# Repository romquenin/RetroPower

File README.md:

# RetroPower

Home Assistant-controlled power module for retro consoles, built around an ESP32-C3 — 2-layer PCB (KiCad), with a relay that emulates the console's power button for remote on/off.

Consoles with a **real power switch** (SNES, NES, Mega Drive, Master System, N64, GameCube, Saturn, Dreamcast, PS1) use this board. Consoles with a **soft / momentary / touch button** (PS2, PS3, PS4 Pro, Xbox OG, Xbox 360, Wii, Wii U) need no PCB at all — just an ESP, one PhotoMOS and one resistor. That variant is documented in [`docs/soft-power-buttons.md`](docs/soft-power-buttons.md).

## Two PCB versions

### `hardware/integrated/` — integrated version (recommended)
The ESP32-C3-Zero module (Waveshare, 18 castellated pins, **antenna version isolated at the end of the board**, see the BOM warning) is **soldered directly to the back of the PCB** — no flying wires. The antenna ends up on the outer edge of the board, completely clear of any copper/metal on both sides, for the best possible WiFi/Bluetooth reception.

- Dimensions: 53.335 x 32.75 mm
- Official KiCad DRC: 0 errors / 0 warnings (v4)
- See `README.md` in this folder for the changelog and the pin-spacing verification procedure to run before soldering the module for good.

### `hardware/compact/` — compact version (fallback)
The ESP32-C3-Zero module is connected via flying wires (not soldered directly onto the PCB). Immune to dimensional variation between modules — useful as a fallback if the integrated version ever runs into a physical compatibility issue.

- Dimensions: 40.45 x 32.75 mm
- Official KiCad DRC: 0 errors / 0 warnings (v11)
- See `README.md` and `WIRING.md` in this folder.

Each folder contains: the `.kicad_pcb`/`.kicad_pro` files, the gerbers (folder + zip), the component position file (`_pos.csv`), the BOM (`BOM.csv`), a rendered image of the routed board, and a `README.md` explaining the design choices.

## Bill of materials

Full per-reference BOM (with placement notes) is in each version's own `BOM.csv` (`hardware/integrated/BOM.csv` / `hardware/compact/BOM.csv`). Same components and values on both versions, except J1 (compact version only, header for the flying wires to the ESP32) and the ESP32 module itself (soldered directly on the integrated version, wired via J1 on the compact one).

**On the PCB:**

| Ref | Part | Package | Notes |
|---|---|---|---|
| U1 | ESP32-C3-Zero (Waveshare) ⚠️ | 18-pin castellated module, 2.54mm pitch | **Version with the antenna at the end of the board, isolated from the other components** (see warning below). Integrated version only: soldered to the back of the PCB |
| K1 | HFD2/003-M-L2-D (Hongfa) | DIP-16 (10 real pins) | Bistable 2xRT relay |
| Q1, Q2 | AO3400A | SOT-23 | N-channel MOSFET |
| D1, D2 | 1N4148WS | SOD-123 | Flyback diodes (relay coils). **Orientation: the stripe (cathode) goes on the OPEN side of the rectangle on the silkscreen** |
| D3 | 1N5819WS | SOD-123 | Reverse-polarity protection on RAW_IN. **Orientation: the stripe (cathode) goes on the CLOSED side of the rectangle on the silkscreen** |
| R1, R2 | 100R | 0805, 1/4W 5% | Series gate resistors |
| R3, R4 | 10k | 0805, 1/4W 5% | Gate pulldowns |
| C1 | 100µF / 16V | SMD electrolytic, 6.3x5.4mm | — |
| C2 | 100nF | 0805 ceramic | HF decoupling on 3V3 |
| J1–J6 | 2.54mm pin headers | 2 to 5 pins, vertical | See each version's wiring notes |

> ⚠️ **Pick the right ESP32-C3 module.** Use the **Waveshare ESP32-C3-Zero** whose ceramic antenna sits **at the end of the board, set apart from the other components**. The PCB is designed so this antenna ends up on the outer edge, clear of any copper. Look-alike boards (clones, "ESP32-C3 Super Mini"…) where the antenna sits among the components, or a different pinout, will give poor Wi-Fi reception and may not fit the footprint. Check the product photos before ordering.

### ESP32-C3-Zero pin order (check before ordering)

The footprint matches the **pin order of the Waveshare ESP32-C3-Zero**. Some look-alike modules use the same size but a **different pin order**: with those, the power and GPIO pins end up in the wrong place. Compare your module with the order below before soldering.

Module seen **from its back side** (the side soldered to the PCB), antenna on the left, USB-C on the right:

| Row | Pins (antenna side → USB-C side) |
|---|---|
| Top (pins 10 → 18) | GP6 · GP7 · GP8 · GP9 · **GP10** · GP18 · GP19 · GP20 · GP21 |
| Bottom (pins 9 → 1) | GP5 · GP4 · **GP3** · GP2 · GP1 · **GP0** · **3V3** · **GND** · 5V |

Pins used by RetroPower:

| Module pin | Signal | Role |
|---|---|---|
| 2 · GND | GND | Common ground |
| 3 · 3V3 | 3V3 | Power from the 3.3 V buck (5V pin stays unconnected) |
| 4 · GP0 | POWER_SENSE | Reads the console state |
| 7 · GP3 | RELAY_SET | Relay SET (turn on) |
| 14 · GP10 | RELAY_RESET | Relay RESET (turn off), also drives the module's RGB LED |

<!-- Photo of the correct module (back side, pin labels visible): add it as docs/images/esp32-c3-zero-pinout.jpg and uncomment the line below.

-->

Full details and the pin-spacing check: [`hardware/integrated/README.md`](hardware/integrated/README.md).

**Off the PCB (external, per console):**

- A buck converter module (raw 12V/8V → regulated 3.3V) — any small off-the-shelf buck board rated for the console's raw voltage works; test it unloaded before wiring it in.
- Hookup wire:
  - **Power lines** (raw 12V/8V to/from the buck, regulated 3V3 to J2): 0.5mm²/20-21AWG is plenty for these currents.
  - **Signal/GPIO lines** (console switch tap to J4/J5, POWER_SENSE tap to J6): thinner wire is fine here, e.g. 30AWG — negligible current, easier to route inside the console's case.

## Firmware

ESPHome configs, in `firmware/`. Duplicate the template that matches your build and change `device_name` / `friendly_name` / the static IP — **one unique IP per console**.

| File | For |
|---|---|
| `retropower_template.yaml` | Relay board + ESP32-C3-Zero (validated on a SNES) |
| `retropower_template_esp8266.yaml` | Relay board + D1 mini (validated on a Master System) |
| `retropower_ps2.yaml` | PS2 fat — relay, momentary button |
| `retropower_megadrive.yaml` | Mega Drive — relay + Reset button (PhotoMOS on GP20) |
| `retropower_ps4.yaml` | PS4 Pro — PhotoMOS, no relay |
| `retropower_xbox_og.yaml` | Xbox OG — PhotoMOS, no relay |
| `retropower_wii.yaml` | Wii — bare ESP-12F + PhotoMOS, no relay |
| `retropower_wiiu.yaml` | Wii U — bare ESP-12F + PhotoMOS, no relay |

Pinout on the **ESP32-C3** board:

- GPIO0 — `POWER_SENSE` (reads the console's 3V3 rail)
- GPIO3 — `RELAY_SET` (100 ms pulse → turns on, via Q1)
- GPIO10 — `RELAY_RESET` (100 ms pulse → turns off, via Q2)

Same board with a **D1 mini** soldered in instead (ESP8266: GPIO0 is a boot strapping pin, GPIO3 is the serial RX and GPIO10 is not brought out, so the three pins have to move):

- GPIO14 / `D5` — `POWER_SENSE`
- GPIO5 / `D1` — `RELAY_SET`
- GPIO4 / `D2` — `RELAY_RESET`

The `D0`–`D8` labels are silkscreen only and have nothing to do with the GPIO numbers — always write the GPIO number in the YAML.

On the **no-relay** builds, a single `output` drives the PhotoMOS (`GPIO4` / `D2`, through a 470 Ω) and `GPIO14` / `D5` reads the sense. The press duration is what distinguishes power-on, standby and forced shutdown, and it has to be measured per console.

## Per-console notes

Measurements, wiring and lessons learned for each console tested so far are in [`docs/consoles/`](docs/consoles/README.md).

## Related projects

- [`projects/toslink-switch-wifi/`](projects/toslink-switch-wifi/README.md) — Wi-Fi control of a CSL 41811 Toslink audio switch (ESPHome on a D1 mini, MOSFET on the IR-jack signal line), so the audio input follows the console that is running.
- [`projects/usb-switch-wifi/`](projects/usb-switch-wifi/README.md) — Wi-Fi USB disk switch: one 2.5" Y-cable disk shared between two consoles (here a Wii U and a Wii) through two bistable relays on a D1 mini board, with a 3D-printable enclosure. The disk follows the Wii automatically and is never taken from a console that is on.

## Generation scripts (KiCad / Python)

`scripts/` contains the Python scripts (using the `pcbnew` API) used to generate and route each board, plus the verification scripts (clearance, holes, connectivity, board-edge clearance, silkscreen, component-body overlap) used alongside KiCad's official DRC.

- `scripts/integrated/`: `build_integrated.py` (placement + footprints), `route_integrated.py` (initial routing), `fix_net_integrated.py` (targeted routing fixes)
- `scripts/compact/`: `build_compact_v3.py`, `route_grid_compact5.py`
- `scripts/checks/`: verification scripts shared by both versions

Requires KiCad 7 (headless `pcbnew` API) and Python 3.

## How it works

The module emulates pressing the console's power button through two separate pulses (SET/RESET) driven by two MOSFETs (Q1/Q2) that control the two coils of a bistable relay (K1) — the relay stays in the chosen state with no continuous power draw. A sense tap (`POWER_SENSE`) lets the ESP32 read the console's actual power state for Home Assistant.

## Power supply

The buck converter (console's raw 12V/8V → regulated 3.3V) is **external**, not integrated onto the PCB. See each version's `README.md`/`WIRING.md` for the exact wiring (`J2` = regulated 3.3V input, `J3` = raw tap + reverse-polarity protection).

## Disclaimer

These files are provided as-is, with no warranty. Always re-run KiCad's official DRC before ordering a batch of PCBs, and check the 3V3 rail with a multimeter before soldering an ESP32 module in for good.

## Assembly notes (validated on a SNES, integrated board)

- **D1/D2 (flyback, 1N4148WS):** in KiCad's `D_SOD-123` footprint pad 1 is the *cathode*. The cathode must go to 3V3, so mount D1/D2 **rotated 180° vs the silkscreen** (stripe toward the 3V3 pad). **D3** is mounted as per the silkscreen.
- **GP0 (U1 pin 4) must be soldered** - it carries POWER_SENSE. Without it Home Assistant never sees the console state.
- Connect the J6 sense wire to the console's 3.3V rail; grounds must be common (buck GND on the console motherboard).
- J4: use COM (square) + NO, in parallel with the original power switch.

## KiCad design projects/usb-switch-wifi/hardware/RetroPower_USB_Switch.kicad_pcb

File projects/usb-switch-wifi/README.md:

# Wi-Fi USB disk switch

Side project, same idea as RetroPower: one 2.5" USB disk shared between two
consoles, switched over Wi-Fi.

Status: **built and working**, sharing one partitioned disk between a
**Wii U** (console 1) and a **Wii** (console 2). The disk follows the Wii
on its own: it goes to the Wii when the Wii turns on, and back to the Wii U
when it turns off.

Why: the Wii crashed when it was switched back on from standby with a USB
disk plugged in (green LED, then everything off, until the mains was
unplugged). Taking the disk away from the Wii whenever it is off removes
the problem, and sharing the disk between two consoles comes for free.

## What it does

A 2.5" disk with a Y cable has two plugs:

- **A**: 5 V + data (D+ / D-) + ground — the main plug;
- **B**: 5 V + ground only — extra current for the disk.

The board has six USB-A sockets: **A** and **B** for the disk, **A1 / B1**
toward console 1, **A2 / B2** toward console 2. Two bistable relays move
the four lines that matter together:

| Relay | Pole 1 | Pole 2 |
|---|---|---|
| K1 | D- | D+ |
| K2 | 5 V of A | 5 V of B |

Common contact on the disk side, NC (relay RESET) toward console 1,
NO (relay SET) toward console 2. Ground stays common to all six sockets.

A change-over contact opens one side before it closes the other, so the two
consoles' 5 V can never be connected together, and the console that is not
selected is completely cut off from the disk.

Same relay, same pinout and same coil driver as RetroPower: one AO3400A per
coil set, 100 Ω gate resistor, 10 kΩ pull-down, a 1N4148WS across each
coil. Both relays move together: Q1 fires both SET coils, Q2 both RESET
coils. The coils run from the D1 mini's 5 V (about 220 mA for two coils,
too much for its 3.3 V regulator); the HFD2/003 coil accepts up to 6 V.

The D1 mini is powered by its own micro-USB, from any 5 V charger. That
5 V never touches the disk's lines: the disk is still powered by the
selected console, exactly as without the switch.

## Board

- 67.8 × 53.2 mm, 2 layers, 1.6 mm thick (the US-306 pins stick out 3.5 mm
  under their body: on a thicker board there is nothing left to solder).
- Gerbers for JLCPCB: [`hardware/gerbers_RetroPower_USB_Switch.zip`](hardware/gerbers_RetroPower_USB_Switch.zip).
- Parts: [`hardware/BOM.csv`](hardware/BOM.csv).
- The board is generated by scripts, KiCad 7 Python (`build_usbswitch.py` →
  placement and nets, `route_usbswitch.py` → FreeRouting 2.0.1 + ground
  pours, `finish_usbswitch.py` → silkscreen + DRC). KiCad DRC: 0 errors.

### Check the USB-A sockets before ordering the PCB

The footprint comes from the seller's drawing of the **US-306** (the
US-307 has the same footprint), which differs from the usual standard
(shell legs 1.45 mm from the pins instead of 2.71 mm). The US-306 sockets
used for the prototype matched it. Generic sockets vary, so if you buy
another model, check with the sockets in hand:

1. distance between the two shell legs, centre to centre: **13.14 mm**;
2. distance between the row of 4 pins and the axis of the legs: **1.45 mm**;
3. spacing of the 4 pins: **2.5 / 2.0 / 2.5 mm** (7.00 mm between the two
   outer ones).

And the one that matters most: **which pin carries 5 V.** Plug a USB
charger into a socket and measure. Socket laid as on the board, opening
toward you, seen from above: **5 V must be the outer pin on the LEFT**
(square pad, pin 1). If it is on the right, the footprint must be mirrored
before ordering — otherwise the consoles' 5 V would end up on the ground
side.

Swapping D+ and D- would not matter: the six sockets are identical and the
data goes straight through.

### Assembly order

1. **The SMD parts under the D1 mini first**: D1–D4, Q1, Q2, R1–R4, C2.
   Once the module is on, they are out of reach. The four diodes are all
   1N4148WS (flyback, one per coil) and go **as printed**: the stripe on the
   **closed side** of the silkscreen rectangle = cathode = 5 V side (no 180°
   trick, unlike RetroPower's D1/D2).
2. C1 (the `+` is marked).
3. The two relays, then the six USB-A sockets.
4. The D1 mini last, flat on its male headers (the enclosure's micro-USB
   opening is sized for that height). Micro-USB on the edge. Only **5V, G,
   D1 and D2** are wired, all on the same row. To make the module easy to
   remove, solder just those four plus **RST** and **3V3** on the other row
   (unconnected pads, they only hold the corners).

Flash the D1 mini over USB **before** soldering it (its USB stays reachable
afterwards anyway, through the enclosure).

## Wiring

- The disk's Y cable: plug **A** into socket **A**, plug **B** into **B**.
- Four **USB-A male to USB-A male** cables, carrying **data** (many cheap
  ones are charge-only and the console will never see the disk):
  **A1 / B1** to console 1 (Wii U), **A2 / B2** to console 2 (Wii).
  **A1 / A2 must go to the port your USB loader reads from.**
- Console 1 is the relays' rest position: put there the console that should
  keep the disk by default.
- A 5 V charger on the D1 mini's micro-USB.

## Firmware

[`usb_switch_wifi.yaml`](usb_switch_wifi.yaml), ESPHome on the D1 mini:

| D1 mini | GPIO | Role |
|---|---|---|
| D2 | GPIO4 | RESET coils → **console 1** |
| D1 | GPIO5 | SET coils → **console 2** |

- In Home Assistant: one select, **"Wii U / Wii"** (names set by
  `console1_name` / `console2_name`), to switch by hand.
- **Automatic mode, in the firmware itself**: when console 2 (the Wii)
  turns on, the disk goes to it; when it turns off, the disk goes back to
  console 1 (the Wii U). No Home Assistant automation needed.
- **The firmware never takes the disk away from a console that is ON**
  (unplugging USB in the middle of a write can corrupt the disk): if the
  Wii U is running and using the disk, switching the Wii on does not steal
  it.
- Both rules need the consoles' RetroPower sensors, read from Home
  Assistant: put their entity IDs in `console1_sensor` / `console2_sensor`,
  and in Home Assistant tick **"Allow the device to perform Home Assistant
  actions"** (Settings → Devices & services → ESPHome → the switch →
  Configure). If Home Assistant is down, the board keeps its position.
- The relays cannot report their position. The firmware stores the last
  choice in flash and, at boot, sends one pulse to that same position: the
  relays are already there, nothing moves, but firmware and relays agree.

## Enclosure

Two parts to print, generated from the board file so the openings fall on
the connectors: [`enclosure/usb_switch_base.stl`](enclosure/usb_switch_base.stl)
and [`enclosure/usb_switch_lid.stl`](enclosure/usb_switch_lid.stl)
(source: `enclosure/usb_switch_enclosure.scad`, OpenSCAD).

- 71.5 × 56.9 × 23.0 mm outside (port labels raised 0.8 mm on the walls).
- Resin (SLA) or FDM. In FDM: PLA or PETG, 0.2 mm layers, no supports; the
  base prints upright, the lid is already exported upside down.
- The board sits on two standoffs and seven small posts under the sockets,
  so plugging a cable presses on plastic, not on the solder joints.
- **2 × M2.5 × 20 mm screws + 2 M2.5 nuts**: each screw goes through the
  lid, a pillar that holds the board down, the board, and into a nut trapped
  under the base.
- Port names **raised on the walls** under each opening (A1 B1 A2 B2 at the
  back, A B 5V at the front), CONSOLE 1 / CONSOLE 2 / DISQUE **engraved
  1 mm deep** on the lid.
- Checked against JLCPCB's SLA resin rules: every wall and every text
  stroke is at least 0.8 mm (walls 1.6 mm, lid 2.4 mm, lip 1.5 mm).
- The cavity is 13 mm tall above the board: the relays are 10.6 mm on the
  datasheet (±0.4 mm), counted as 12 mm after measuring, plus 1 mm. Other
  relays: change `INNER_H` in the generator and re-export.
- The micro-USB opening assumes the connector is centred on the D1 mini, as
  on the WEMOS original. Check your clone.

## Known limits

- **USB 2.0 high speed through a general-purpose relay.** The HFD2 datasheet
  gives no high-frequency figures. It works in practice (games load from the
  disk on both consoles), like the mechanical USB 2.0 sharing switches that
  do the same thing, and the data path is short. If you rely on it for big
  copies, check a large file once.
- Both consoles' grounds are joined through the board. They usually are
  already, through the TV.

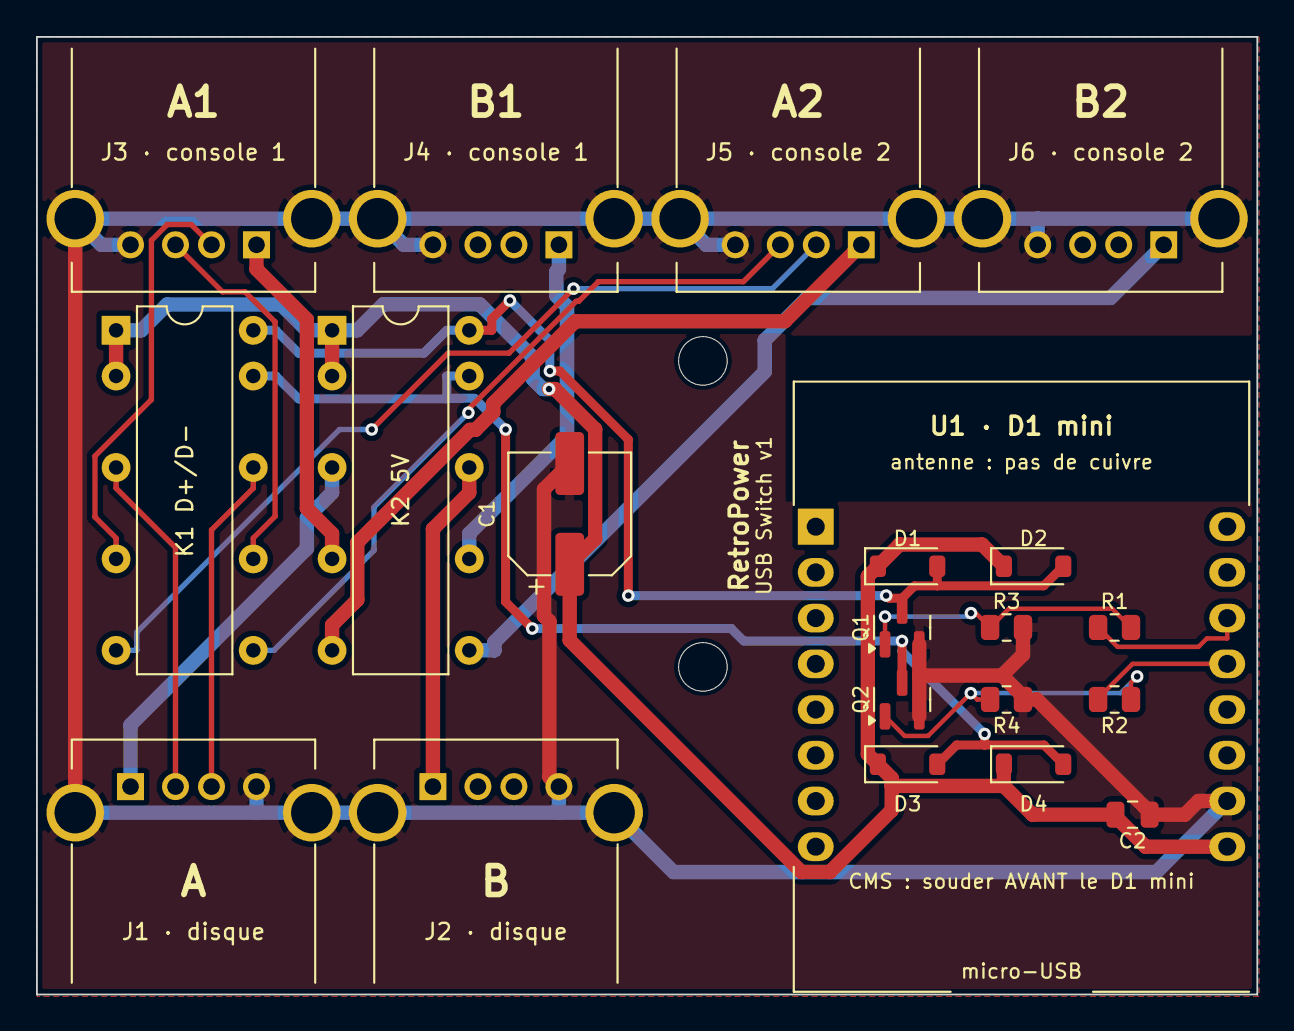
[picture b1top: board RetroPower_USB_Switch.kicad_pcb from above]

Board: 2 copper layers, 67.8 x 53.2 mm, 23 parts (0 on the bottom side), 20 nets.

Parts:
C1: 100uF/16V; CP_Elec_6.3x5.4
C2: 100nF; C_0805_2012Metric
D1, D2, D3, D4: 1N4148WS; D_SOD-123
H1, H2: M2.5; MountingHole_2.7mm_M2.5
J1: USB-A US-306 (A); USB_A_US-306_Horizontal
J2: USB-A US-306 (B); USB_A_US-306_Horizontal
J3: USB-A US-306 (A1); USB_A_US-306_Horizontal
J4: USB-A US-306 (B1); USB_A_US-306_Horizontal
J5: USB-A US-306 (A2); USB_A_US-306_Horizontal
J6: USB-A US-306 (B2); USB_A_US-306_Horizontal
K1: HFD2/003-M-L2-D (data); DIP-16_W7.62mm
K2: HFD2/003-M-L2-D (5V); DIP-16_W7.62mm
Q1, Q2: AO3400A; SOT-23
R1, R2: 100R; R_0805_2012Metric
R3, R4: 10k; R_0805_2012Metric
U1: WEMOS D1 mini; WEMOS_D1_mini_light

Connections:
+5V: C1.1, C2.1, D1.1, D2.1, D3.1, D4.1, K1.1, K1.2, K2.1, K2.2, U1.9
C1_DM: J3.2, K1.6
C1_DP: J3.3, K1.11
C1_VA: J3.1, K2.6
C1_VB: J4.1, K2.11
C2_DM: J5.2, K1.8
C2_DP: J5.3, K1.9
C2_VA: J5.1, K2.8
C2_VB: J6.1, K2.9
CTL_RST: R2.1, U1.13
CTL_SET: R1.1, U1.14
DSK_DM: J1.2, K1.4
DSK_DP: J1.3, K1.13
DSK_VA: J1.1, K2.4
DSK_VB: J2.1, K2.13
GND: C1.2, C2.2, J1.4, J1.5, J2.4, J2.5, J3.4, J3.5, J4.4, J4.5, J5.4, J5.5, J6.4, J6.5, Q1.2, Q2.2, R3.2, R4.2, U1.10
G_RST: Q2.1, R2.2, R4.1
G_SET: Q1.1, R1.2, R3.1
RST_DRV: D3.2, D4.2, K1.15, K2.15, Q2.3
SET_DRV: D1.2, D2.2, K1.16, K2.16, Q1.3

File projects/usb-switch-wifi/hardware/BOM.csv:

Reference,Qty,Value,Footprint,Notes
J1-J6,6,USB-A female right angle US-306,usbswitch:USB_A_US-306_Horizontal,"Generic AliExpress US-306. Footprint drawn from the seller's PCB layout: pins 7.00 / 2.00 mm, d0.92; legs 13.14 mm apart, d2.30, 1.45 mm toward the opening. Pin 1 = square pad = 5 V. BEFORE ORDERING THE PCB: check the 3 dimensions and which pin carries 5 V (see README). J1 = A (disk), J2 = B (disk), J3 = A1, J4 = B1 (console 1), J5 = A2, J6 = B2 (console 2)."
K1,1,HFD2/003-M-L2-D,Package_DIP:DIP-16_W7.62mm,"Bistable relay, D- (pole 1) and D+ (pole 2). Same relay and pinout as RetroPower. Only 10 pins: the 6 unused DIP-16 holes are removed."
K2,1,HFD2/003-M-L2-D,Package_DIP:DIP-16_W7.62mm,"Bistable relay, 5V_A (pole 1) and 5V_B (pole 2). Coils driven at 5 V (max 6 V for the 003 coil)."
Q1,1,AO3400A,Package_TO_SOT_SMD:SOT-23,"Drives both SET coils (console 2). Under the D1 mini."
Q2,1,AO3400A,Package_TO_SOT_SMD:SOT-23,"Drives both RESET coils (console 1). Under the D1 mini."
D1-D4,4,1N4148WS,Diode_SMD:D_SOD-123,"Flyback diodes, one per coil. Mount AS PRINTED: silkscreen bar = cathode = +5V side (no 180 deg trick, unlike RetroPower D1/D2). Under the D1 mini."
R1-R2,2,100R,Resistor_SMD:R_0805_2012Metric,"Gate series resistors. Under the D1 mini."
R3-R4,2,10k,Resistor_SMD:R_0805_2012Metric,"Gate pull-downs. Under the D1 mini."
C1,1,100uF/16V,Capacitor_SMD:CP_Elec_6.3x5.4,"Reservoir for the coil pulses (two coils at once, ~220 mA). '+' marked on the silkscreen."
C2,1,100nF,Capacitor_SMD:C_0805_2012Metric,"5 V decoupling. Under the D1 mini."
U1,1,WEMOS D1 mini + 2 x 1x8 male headers,Module:WEMOS_D1_mini_light,"Soldered on its male headers, LAST, after the SMD parts below it. Only 5V, G, D1, D2 are wired; the other row is for mechanics. Antenna end toward the inside, micro-USB on the board edge."
H1-H2,2,M2.5 mounting hole,MountingHole:MountingHole_2.7mm_M2.5,"Enclosure: M2.5 x 20 mm screw from the lid, nut trapped under the base."

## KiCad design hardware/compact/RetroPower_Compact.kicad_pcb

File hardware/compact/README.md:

RetroPower - Central module, COMPACT version -- fix for 3 copper_edge_clearance errors
========================================================================
Dimensions: 40.45 x 32.75mm (UNCHANGED). Component layout UNCHANGED.
Schematic/wiring UNCHANGED (D3 remains correct, see previous version).

WHY THIS NEW VERSION
------------------------------------
Your last official DRC run found 3 [copper_edge_clearance] errors -- all
on the Q1_GATE net (the trace connecting R1, Q1 and R3), at three
different spots: (10.4, 0.2), (24.4, 0.2) and (4.8, 5.8). In all three
cases, KiCad measured only 0.025mm between this trace and the board
outline (Edge.Cuts), while the board's rules require 0.5mm.

WHAT THIS ACTUALLY MEANS
--------------------------------------
The "board outline" (Edge.Cuts) is the line the manufacturer's router (or
laser) follows to cut your board out of the raw copper/fiberglass panel.
This cut is never perfectly precise -- there's always a small mechanical
tolerance. If a copper trace runs too close to this cut line (here, 25
microns -- about the width of a fine hair), there's a real risk the
cutter "eats into" part of the trace, or even severs it completely,
without this necessarily being visible to the naked eye. Hence the 0.5mm
safety margin rule.

WHERE THIS CAME FROM
-------------------
My targeted fix tool (the one I use to repair a single copper trace
without touching the rest of the board) did have a safety margin near
the board outline, but it was only 0.3mm -- below the 0.5mm actually
required. Since the Q1_GATE net is precisely the one I had to repair
several times during the D3 fix (the board is very dense in that area,
squeezed between relay K1 and several other traces), it's the only one
that ended up going through that tool with an insufficient margin --
which explains why it alone was affected.

Digging further (checking that the fixed trace really respects 0.5mm
everywhere, not just at the 3 spots your DRC flagged), I found a second,
more subtle issue in that same tool: the safety margin near the edge
didn't account for a via's own size (a connection pad between the two
copper layers, 0.4mm radius) -- it only protected its center, not its
actual outline. A via could therefore have been allowed at a spot where
its own body still ran too close to the edge. Also fixed: the margin is
now computed separately for a trace (0.5mm + half the trace width) and
for a via (0.5mm + its actual radius).

WHAT WAS FIXED
------------------------
1. The safety margin near the board outline, in the targeted fix tool,
   was changed from 0.3mm to a value that always guarantees at least
   0.5mm of real copper clearance at the edge -- separately for traces
   and for vias (see above).
2. The Q1_GATE net was entirely ripped up and rerouted with this
   corrected margin. Since the area is very congested (the direct path
   between Q1 and R1/R3 is blocked on both sides by the already-placed
   3V3, GND and RESET_CTRL traces), it had to be routed with a finer
   calculation grid to find a path that respects both the 0.5mm board-
   edge margin AND the 0.2mm minimum trace/pad clearance -- both were
   possible to satisfy together, just not with the coarse calculation
   grid used until then.
3. A new verification tool was built specifically for this rule (none of
   my previous tools checked the board outline at all -- a complete
   blind spot, now covered). It first reproduced EXACTLY the 3 values
   from your official DRC (0.025mm at the same three coordinates) before
   I fixed anything, to make sure it was measuring the same thing as
   KiCad before relying on it to validate the fix.

WHAT WAS RE-VERIFIED (the whole board, not just Q1_GATE)
--------------------------------------------------------------------
- Distance to the board outline (new rule checked): 0 violations across
  the whole board (0 traces, 0 vias, 0 pads closer than 0.5mm from the
  edge).
- Electrical clearance (exact pad geometry, vias included): 0 violations
  across 558 elements.
- Real connectivity (correct copper layer everywhere): 0 open circuits,
  0 dangling ends.
- Hole-to-hole spacing: 0 violations across 82 holes.
- Silkscreen overlap: 0 overlaps.
- Component body overlap: 0 real overlaps (the 7 already-known and
  accepted 0.25-0.30mm close calls from the start of the project remain,
  confirmed harmless by your own DRC across several versions).

Nothing else changed on the board: same component placement, same
electrical schematic (D3 correct), same dimensions. Only the physical
path of the Q1_GATE trace changed to respect the edge safety margin.

WHAT'S LEFT TO DO BEFORE ORDERING
---------------------------------------------
1. IMPORTANT: re-run KiCad's official DRC on this fixed file -- as
   always, that check matters most.
2. Visually review the routing on screen, area by area (the Q1_GATE path
   is a bit more winding than before because of the very limited space
   around K1 -- that's normal and expected, it remains a continuous
   trace with 0 defects).
3. Measure the ESP32 board you're actually using to confirm the "ESP32
   zone" rectangle roughly matches.
4. The buck stays external and MUST be tested unloaded before wiring it
   in.
5. Check that 40.45 x 32.75mm fits the intended enclosure before
   ordering fabrication.
6. Before plugging in the ESP32 for the first time: measure the voltage
   on the PCB's 3V3 rail with a multimeter (between a 3V3 pad and a GND
   pad) BEFORE inserting the ESP32 module -- you should read ~3.3V, not
   ~12V (verification of the D3 fix, still valid).

FILES PROVIDED
-------------------
- RetroPower_Compact.kicad_pcb: the complete, fixed PCB (open in KiCad)
- RetroPower_Compact.kicad_pro: minimal project file
- gerbers_RetroPower_Compact.zip: Gerbers + drill + position file
- RetroPower_Compact_pos.csv: position/orientation of each component
- BOM.csv: component list (unchanged from the previous version)
- final_compact.png: visual render of the fixed routing

Board dimensions: 40.45 x 32.75 mm, no mounting holes.

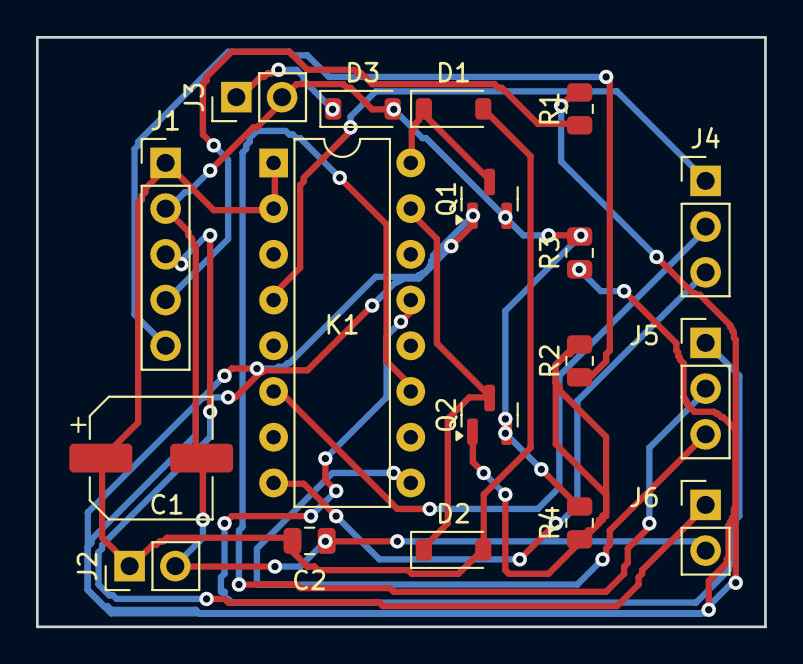
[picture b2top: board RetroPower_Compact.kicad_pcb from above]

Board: 2 copper layers, 40.5 x 32.8 mm, 18 parts (0 on the bottom side), 16 nets.

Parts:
C1: 100uF/16V (CMS); CP_Elec_6.3x5.4
C2: 100nF; C_0805_2012Metric
D1, D2: 1N4148WS (SOD-123); D_SOD-123
D3: 1N5819WS (SOD-123); D_SOD-123
J1: ESP32 (fils volants); PinHeader_1x05_P2.54mm_Vertical
J2: Buck 3V3 OUT; PinHeader_1x02_P2.54mm_Vertical
J3: Tap alim brute (vers buck); PinHeader_1x02_P2.54mm_Vertical
J4: Switch console (pole 1); PinHeader_1x03_P2.54mm_Vertical
J5: Pole 2 relais (libre/reserve); PinHeader_1x03_P2.54mm_Vertical
J6: POWER_SENSE tap console (deja 3.3V); PinHeader_1x02_P2.54mm_Vertical
K1: HFD2/003-M-L2-D; DIP-16_W7.62mm
Q1, Q2: AO3400A; SOT-23
R1, R2: 100R; R_0805_2012Metric
R3, R4: 10k; R_0805_2012Metric

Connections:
3V3: C1.1, C2.1, D1.2, D2.2, J1.1, J2.1, K1.1, K1.2
COIL_RESET_B: D2.1, K1.15, Q2.3
COIL_SET_B: D1.1, K1.16, Q1.3
GND: C1.2, C2.2, D3.2, J1.2, J2.2, J3.2, J6.2, Q1.2, Q2.2, R3.2, R4.2
Q1_GATE: Q1.1, R1.2, R3.1
Q2_GATE: Q2.1, R2.2, R4.1
RAW_IN: D3.1, J3.1
RESET_CTRL: J1.5, R2.1
SENSE_MID: J1.3, J6.1
SET_CTRL: J1.4, R1.1
SW2_COM: J5.1, K1.13
SW2_NC: J5.2, K1.11
SW2_NO: J5.3, K1.9
SW_COM: J4.1, K1.4
SW_NC: J4.2, K1.6
SW_NO: J4.3, K1.8
